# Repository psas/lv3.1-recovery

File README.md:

# LV-3.1 Recovery Repository

The LV-3.1 Electromechanical Recovery System (ERS) is a fully-resettable recovery system for the [PSAS](http://psas.pdx.edu/) Launch Vehicle v 3.1 (LV-3.1). Each ERS "unit" releases a single parachute. The top unit deploys our ballute test parachute that's in the nose cone, the next ERS unit releases a standard drogue, and the final ERS unit releases the main parachute.

## Mechanical CAD
All mechanical CAD has been moved to OnShape and can be found [here](https://cad.onshape.com/documents/03e169a7501c9614bcd8fe34/w/d2206dc55680e29e4d8f6e15/e/43f9d4697ebc459acca1436a).

## Control System

In this Git repo is a PCB with STM32F091 microcontroller that controls the system. See the ControlSystem directory.

## Testing and Analysis

The ERS system will be tested by dropping it from a helicopter over a field. Many parameters must be considered for this test including wind speed, altitude, field size, parachute drag coefficients, and parachute release timing. Analysis of drop test dispersal patterns based on fixing some parameters and simulating variation in others enables us to choose an appropriate drop site and drop parameters. Analysis notebooks can by found in the /analysis directory.

* [Parent Directory](https://github.com/psas/lv3.1-recovery/tree/master/Analysis)
* [Primary mission analysis document](https://github.com/psas/lv3.1-recovery/blob/master/Analysis/Mission_Analysis.ipynb)
* [Jupyter Notebook to run simulations](https://github.com/psas/lv3.1-recovery/blob/master/Analysis/drop_test_simulator.ipynb)

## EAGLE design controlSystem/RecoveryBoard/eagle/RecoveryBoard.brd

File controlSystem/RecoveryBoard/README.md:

# Electromechanical Recovery System (ERS) v4.0 Controller Board 

## General information
This board controls the ERS v4 modules in LV3.1 and hopefully eventually in LV4.

Full documentation can be found [here](https://docs.google.com/document/d/1TOoC-d3vpsw2uvtvazEmFV9_g59nFPVRWKC9Ye5qgKw/edit?usp=sharing)

## Firmware

The firmware is written in C and runs on top of ChibiOS, a small RTOS. See the "firmware" directory. The [oresat-firmware](https://github.com/oresat/oresat-firmware) repository has instructions on how to get started on the tool chain.

## License

All materials in this repo are copyright Portland State Aerospace Society and are licensed under the CERN Open Hardware Licence Version 2 -
Strongly Reciprocal (CERN-OHL-S v2), or any later version. A copy of the license is located in [here](LICENSE.md).

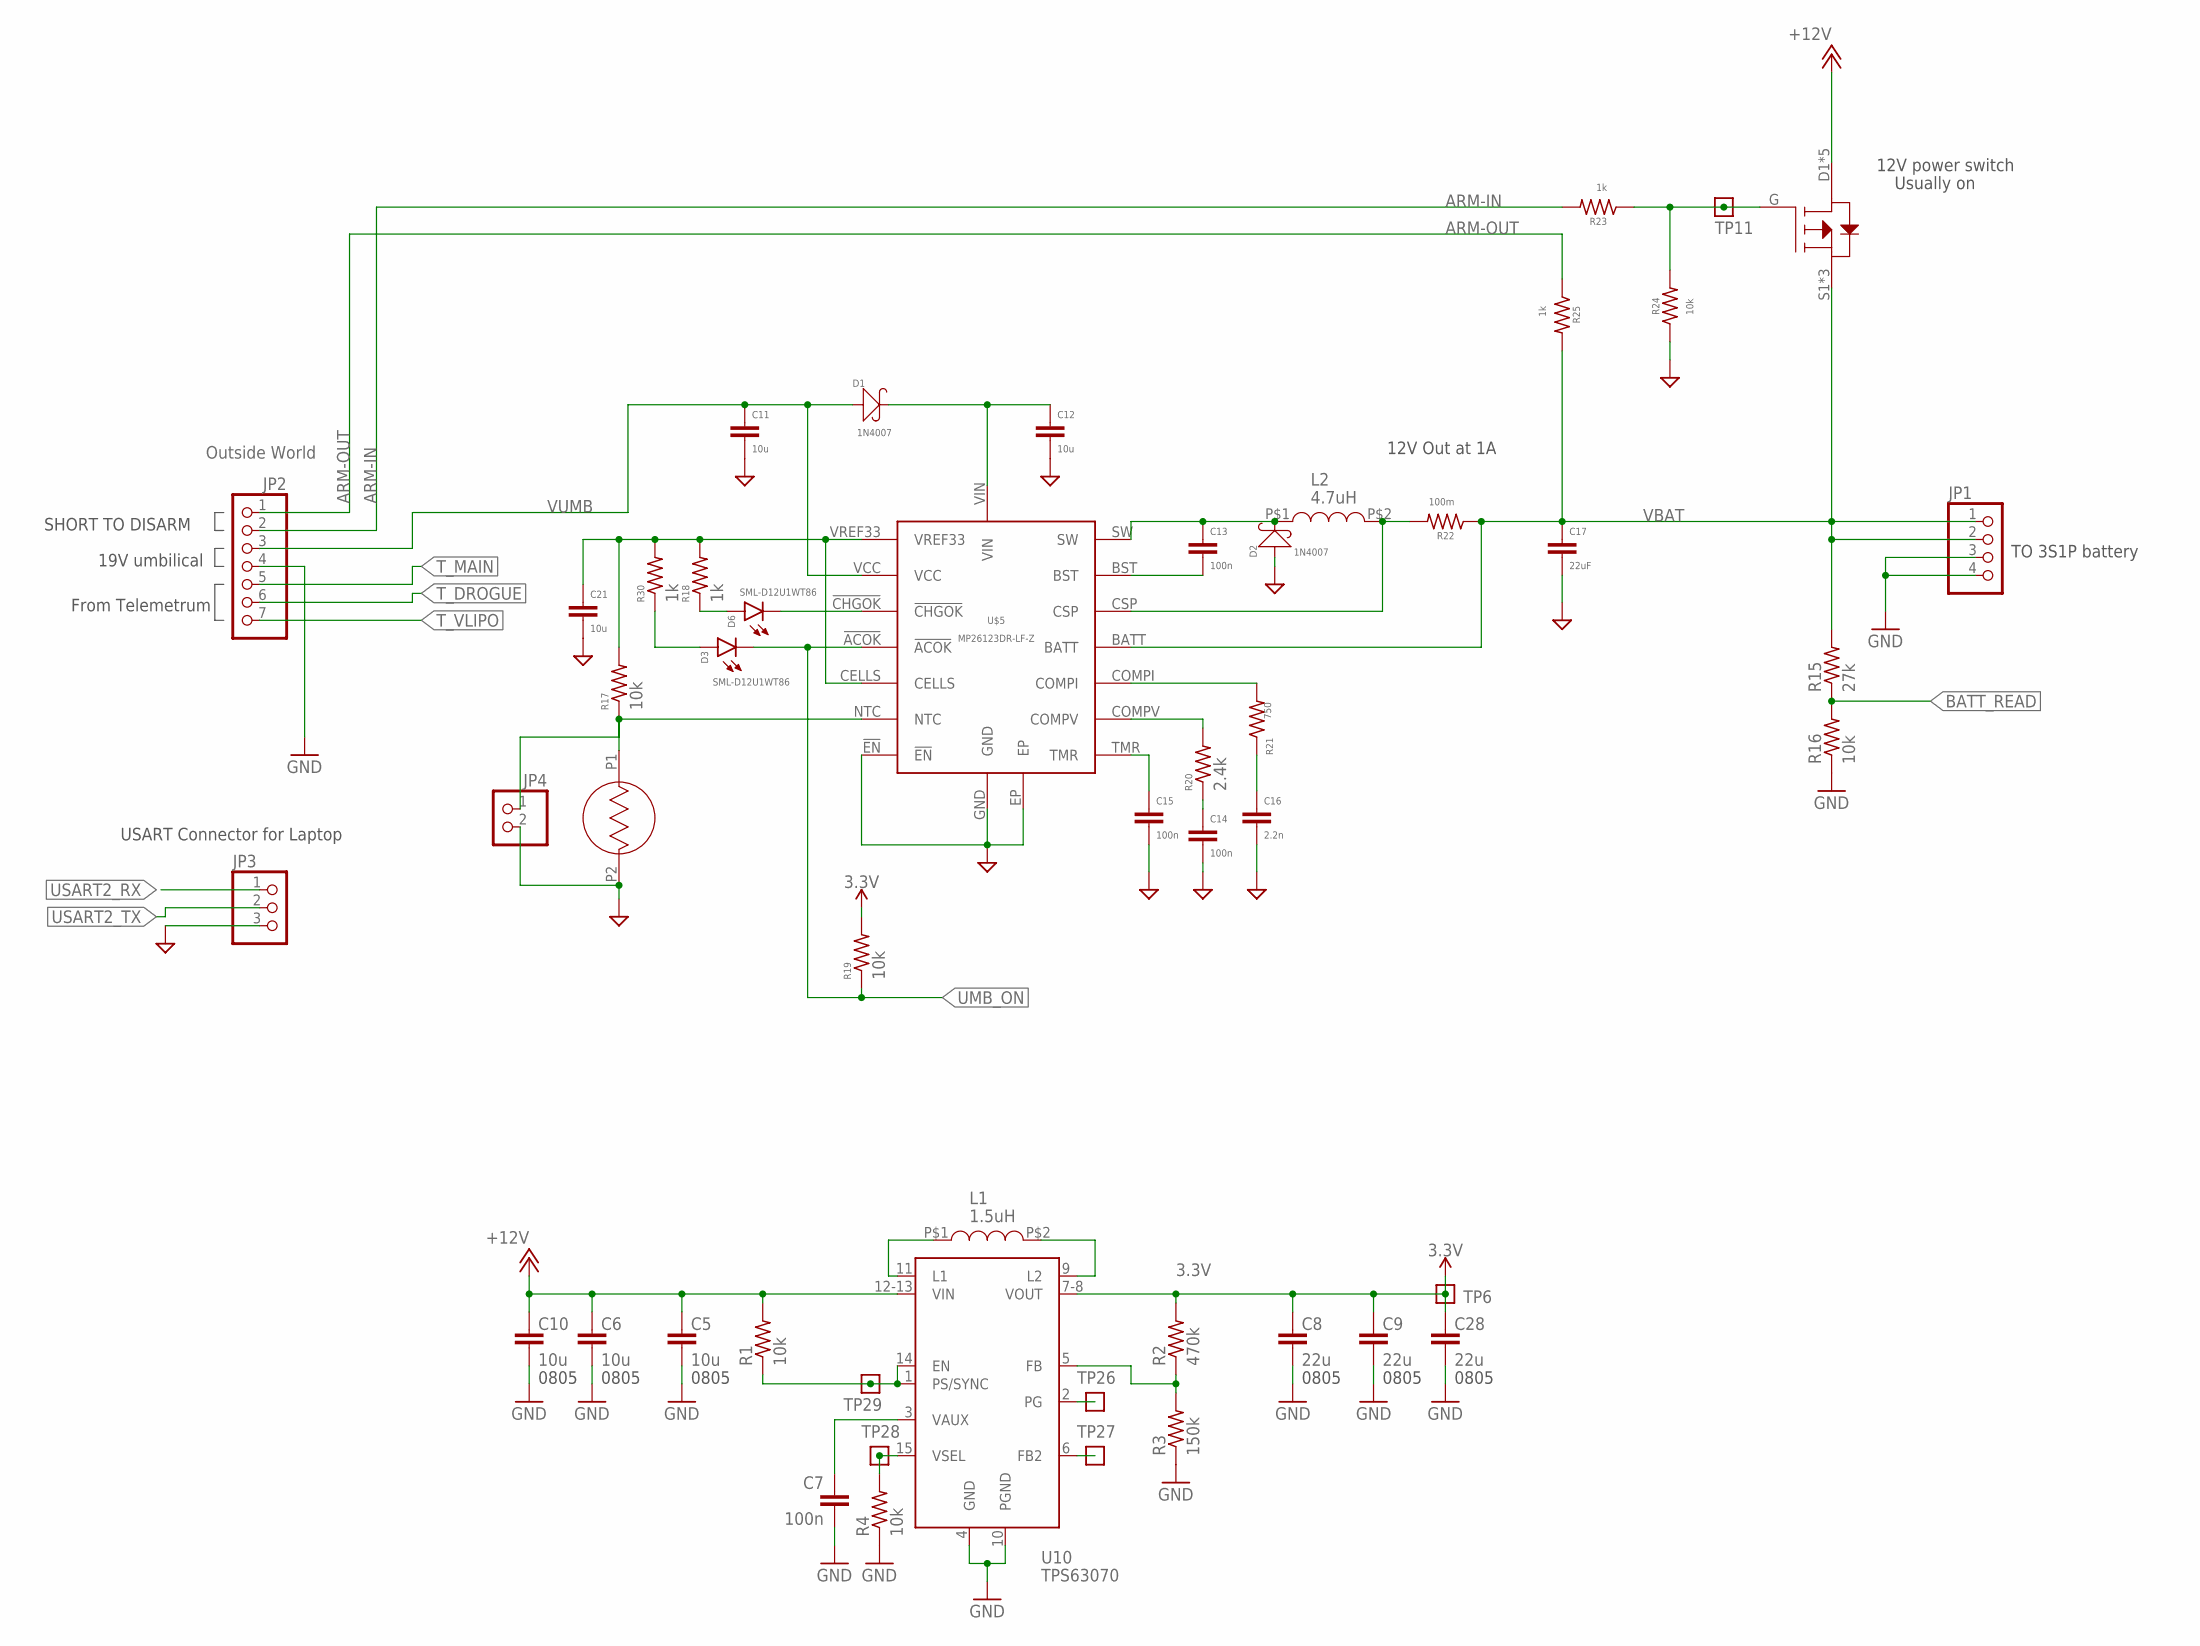
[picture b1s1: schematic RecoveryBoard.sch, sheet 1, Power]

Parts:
C5: 10u; .0805-C-NOSILK; MPN CL05B104KO5NNNC
C6, C10, C11, C12, C21: 10u; .0805-C-NOSILK
C7: 100n; .0603-C-NOSILK; MPN CL05B104KO5NNNC
C8: 22u; .0805-C-NOSILK; MPN CL05B104KO5NNNC
C9, C28: 22u; .0805-C-NOSILK
C13, C14, C15: 100n; .0603-C-NOSILK
C16: 2.2n; .0603-C-NOSILK
C17: 22uF; .0805-C-NOSILK
D1, D2: 1N4007; DO-214AC
D3, D6: SML-D12U1WT86; CHIPLED_0603; MPN SML-D12U1WT86
JP1: PINHD-1X4; 1X04
JP2: PINHD-1X7; 1X07
JP3: PINHD-1X3; 1X03
JP4: PINHD-1X2; 1X02
L1: 1.5uH; IHLP2020CZER1R5M11
L2: 4.7uH; IHLP2020BZER4R7M11
Q7: SI7465DP-T1-E3; SI7465DP-T1-E3CT-ND
R1, R4, R16: 10k; .0603-C-NOSILK; MPN RC1005F6653CS
R2: 470k; .0603-C-NOSILK; MPN RC1005F6653CS
R3: 150k; .0603-C-NOSILK; MPN RC1005F6653CS
R5: NHQ103B375T10
R15: 27k; .0603-C-NOSILK; MPN RC1005F6653CS
R17, R19, R24: 10k; .0603-C-NOSILK
R18, R23, R25, R30: 1k; .0603-C-NOSILK
R20: 2.4k; .0603-C-NOSILK
R21: 750; .0603-C-NOSILK
R22: 100m; 1206-C
TP6, TP11, TP26, TP27, TP28, TP29: TEST-POINT; 2MM-TEST-POINT
U10: TPS63070; TPS63070X
U$5: MP26123DR-LF-Z

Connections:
3.3V: C8.1, C9.1, C28.1, R2.2, R19.2, TP6.1, U10.7-8 (VOUT); also elsewhere on the board
!BEN: C12.1, D1.2 (-), U$5.VIN
+12V: C5.1, C6.1, C10.1, Q7.D1 (D), Q7.D2 (D), Q7.D3 (D), Q7.D4 (D), Q7.DPAD (D), R1.2, U10.12-13 (VIN); also elsewhere on the board
ARM-IN: JP2.2, R23.2
ARM-OUT: JP2.1, R25.1
BATT_READ: R15.1, R16.2; also elsewhere on the board
GND: C5.2, C6.2, C7.2, C8.2, C9.2, C10.2, C11.2, C12.2, C14.2, C15.2, C16.2, C17.2, C21.2, C28.2, D2.1 (+), JP1.3, JP1.4, JP2.4, JP3.3, JP4.2, R3.1, R4.1, R5.P2, R16.1, R24.1, U10.4 (GND), U10.10 (PGND), U$5.!EN, U$5.EP, U$5.GND; also elsewhere on the board
unnamed: C13.1, D2.2 (-), L2.P$1, U$5.SW
unnamed: C13.2, U$5.BST
unnamed: C21.1, R17.2, R18.2, R30.2, U$5.CELLS, U$5.VREF33
unnamed: D6.C, U$5.!CHGOK
unnamed: D3.A, R30.1
unnamed: Q7.G, R23.1, R24.2, TP11.1
unnamed: D6.A, R18.1
unnamed: R20.2, U$5.COMPV
unnamed: C15.1, U$5.TMR
unnamed: JP4.1, R5.P1, R17.1, U$5.NTC
unnamed: R21.2, U$5.COMPI
unnamed: C16.1, R21.1
unnamed: L2.P$2, R22.2, U$5.CSP
unnamed: C14.1, R20.1
TPS-EN: R1.1, TP29.1, U10.1 (PS/SYNC), U10.14 (EN)
TPS-FB: R2.1, R3.2, U10.5 (FB)
TPS-FB2: TP27.1, U10.6 (FB2)
TPS-L1: L1.P$1, U10.11 (L1)
TPS-L2: L1.P$2, U10.9 (L2)
TPS-PG: TP26.1, U10.2 (PG)
TPS-VAUX: C7.1, U10.3 (VAUX)
TPS-VSEL: R4.2, TP28.1, U10.15 (VSEL)
T_DROGUE: JP2.6; also elsewhere on the board
T_MAIN: JP2.5; also elsewhere on the board
T_VLIPO: JP2.7; also elsewhere on the board
UMB_ON: D3.C, R19.1, U$5.!ACOK; also elsewhere on the board
USART2_RX: JP3.1; also elsewhere on the board
USART2_TX: JP3.2; also elsewhere on the board
VBAT: C17.1, JP1.1, JP1.2, Q7.S1 (S), Q7.S2 (S), Q7.S3 (S), R15.2, R22.1, R25.2, U$5.BATT
VUMB: C11.1, D1.1 (+), JP2.3, U$5.VCC

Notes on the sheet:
0805
Outside World
TO 3S1P battery
SHORT TO DISARM
19V umbilical
12V power switch
Usually on
From Telemetrum
USART Connector for Laptop
12V Out at 1A

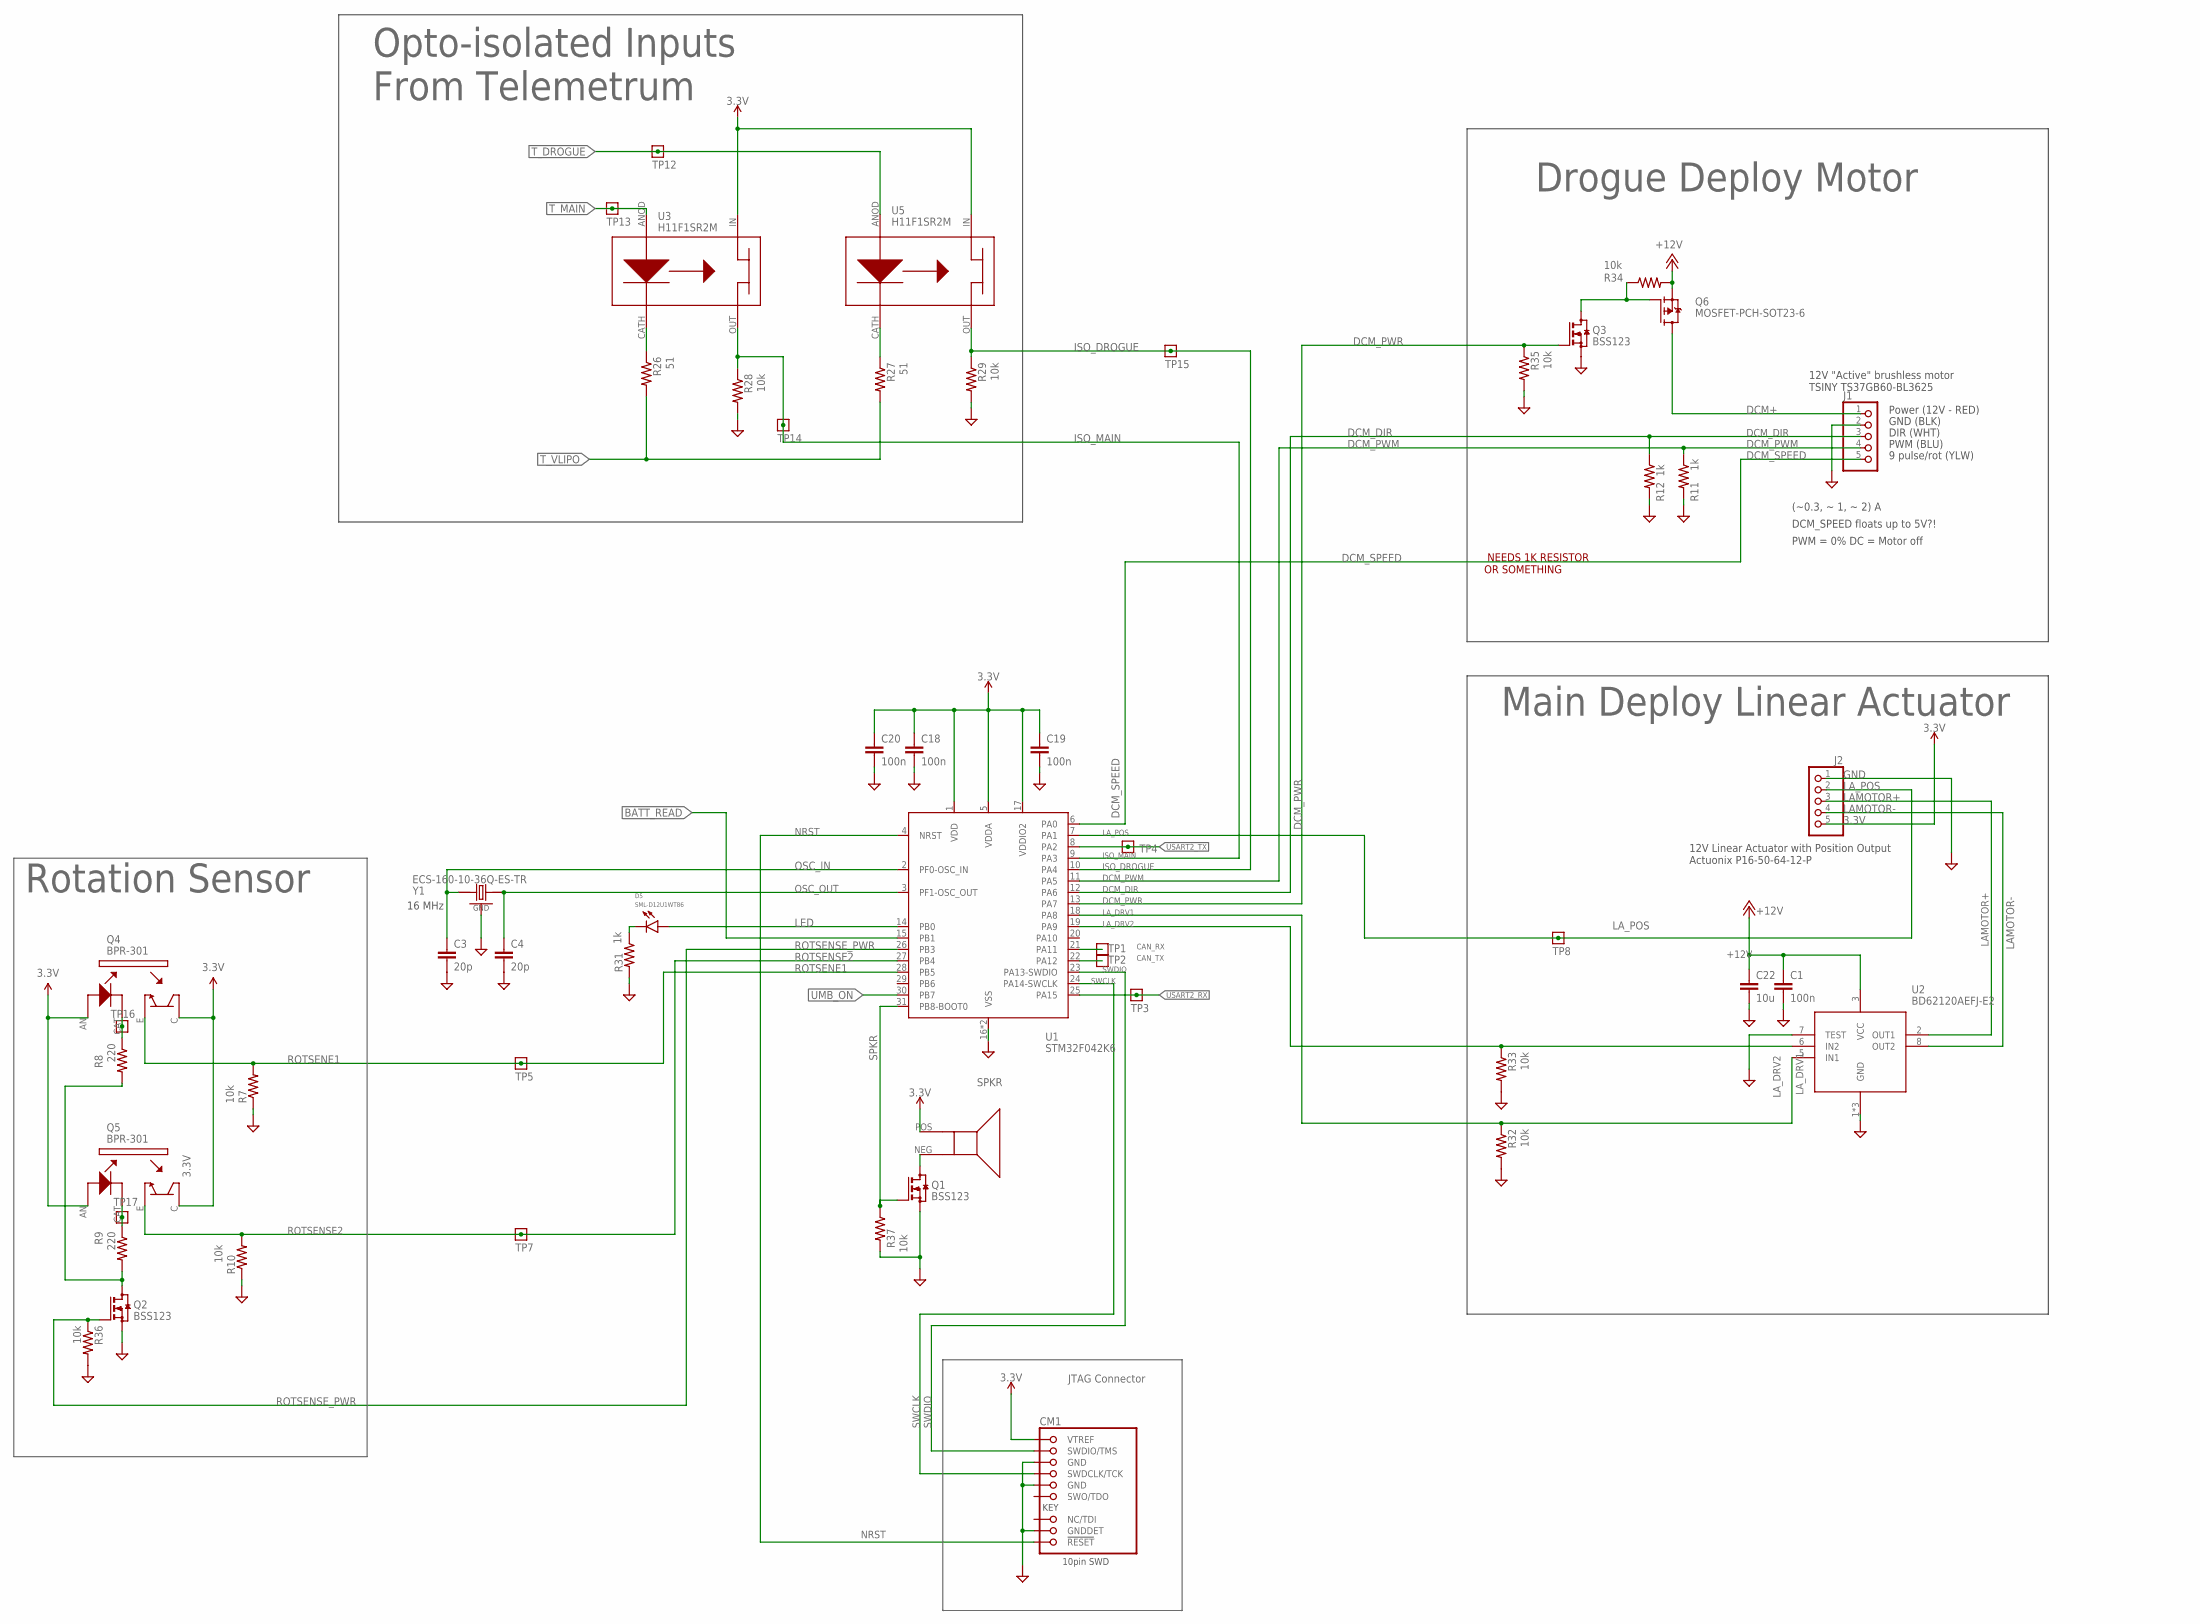
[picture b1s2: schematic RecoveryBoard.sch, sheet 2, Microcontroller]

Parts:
C1, C18, C19, C20: 100n; .0603-C-NOSILK
C3, C4: 20p; .0603-C-NOSILK
C22: 10u; .0805-A-NOSILK
CM1: FTSH-105-XX-X-DV-K; CON10_2X5_DUK_FTSH
D5: SML-D12U1WT86; CHIPLED_0603; MPN SML-D12U1WT86
J1, J2: PINHD-1X5; 1X05
Q1, Q2, Q3: BSS123; SOT23
Q4, Q5: BPR-301
Q6: MOSFET-PCH-SOT23-6; SOT23-6
R7, R10, R28, R29, R32, R33, R34, R35, R36, R37: 10k; .0603-C-NOSILK
R8, R9: 220; .0603-C-NOSILK
R11, R12, R31: 1k; .0603-C-NOSILK
R26, R27: 51; .0603-C-NOSILK
TP1, TP2, TP3, TP4, TP5, TP7, TP8, TP12, TP13, TP14, TP15, TP16, TP17: TEST-POINT; 2MM-TEST-POINT
U1: STM32F042K6; QFP32-7X7
U2: BD62120AEFJ-E2; SOIC127P600X100-9N
U3, U5: H11F1SR2M
U$7: SMT-0440-S-R
Y1: ECS-160-10-36Q-ES-TR; XTAL_ECS-160-10-36Q-ES-TR

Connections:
3.3V: C18.1, C19.1, C20.1, CM1.1 (VTREF), J2.5, Q4.AN (ANOD), Q4.C (COLL), Q5.AN (ANOD), Q5.C (COLL), U1.1 (VDD), U1.5 (VDDA), U1.17 (VDDIO2), U3.IN, U5.IN, U$7.POS; also elsewhere on the board
+12V: C1.1, C22.1, Q6.4 (S), R34.2, U2.3 (VCC); also elsewhere on the board
BATT_READ: U1.15 (PB1); also elsewhere on the board
CAN_RX: TP1.1, U1.21 (PA11)
CAN_TX: TP2.1, U1.22 (PA12)
DCM+: J1.1, Q6.1 (D), Q6.2 (D), Q6.5 (D), Q6.6 (D)
DCM_DIR: J1.3, R12.1, U1.12 (PA6)
DCM_PWM: J1.4, R11.1, U1.11 (PA5)
DCM_PWR: Q3.1 (G), R35.1, U1.13 (PA7)
DCM_SPEED: J1.5, U1.6 (PA0)
GND: C1.2, C3.2, C4.2, C18.2, C19.2, C20.2, C22.2, CM1.3 (GND), CM1.5 (GND), CM1.9 (GNDDET), J1.2, J2.1, Q1.2 (S), Q2.2 (S), Q3.2 (S), R7.1, R10.1, R11.2, R12.2, R28.2, R29.2, R31.2, R32.2, R33.2, R35.2, R36.2, R37.2, U1.16 (VSS), U1.32 (VSS), U2.1 (GND), U2.4 (GND), U2.7 (TEST), U2.9 (GND), Y1.GND, Y1.GND2 (GND); also elsewhere on the board
ISO_DROGUE: R29.1, TP15.1, U1.10 (PA4), U5.OUT
ISO_MAIN: R28.1, TP14.1, U1.9 (PA3), U3.OUT
LAMOTOR+: J2.3, U2.2 (OUT1)
LAMOTOR-: J2.4, U2.8 (OUT2)
LA_DRV1: R32.1, U1.18 (PA8), U2.5 (IN1)
LA_DRV2: R33.1, U1.19 (PA9), U2.6 (IN2)
LA_POS: J2.2, TP8.1, U1.7 (PA1)
LED: D5.A, U1.14 (PB0)
unnamed: Q1.3 (D), U$7.NEG
unnamed: Q4.CAT (CATH), R8.1, TP16.1
unnamed: D5.C, R31.1
unnamed: Q5.CAT (CATH), R9.1, TP17.1
unnamed: Q3.3 (D), Q6.3 (G), R34.1
unnamed: R26.1, U3.CATH (CAT)
unnamed: R27.1, U5.CATH (CAT)
unnamed: Q2.3 (D), R8.2, R9.2
NRST: CM1.10 (!RESET), U1.4 (NRST)
OSC_IN: C3.1, U1.2 (PF0-OSC_IN), Y1.IN/OUT
OSC_OUT: C4.1, U1.3 (PF1-OSC_OUT), Y1.OUT/IN
ROTSENE1: Q4.E (EMIT), R7.2, TP5.1, U1.28 (PB5)
ROTSENSE2: Q5.E (EMIT), R10.2, TP7.1, U1.27 (PB4)
ROTSENSE_PWR: Q2.1 (G), R36.1, U1.26 (PB3)
SPKR: Q1.1 (G), R37.1, U1.31 (PB8-BOOT0)
SWCLK: CM1.4 (SWDCLK/TCK), U1.24 (PA14-SWCLK)
SWDIO: CM1.2 (SWDIO/TMS), U1.23 (PA13-SWDIO)
T_DROGUE: TP12.1, U5.ANOD; also elsewhere on the board
T_MAIN: TP13.1, U3.ANOD; also elsewhere on the board
T_VLIPO: R26.2, R27.2; also elsewhere on the board
UMB_ON: U1.30 (PB7); also elsewhere on the board
USART2_RX: TP3.1, U1.25 (PA15); also elsewhere on the board
USART2_TX: TP4.1, U1.8 (PA2); also elsewhere on the board

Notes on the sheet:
Rotation Sensor
JTAG Connector
12V Linear Actuator with Position Output Actuonix P16-50-64-12-P
12V "Active" brushless motor TSINY TS37GB60-BL3625
Power (12V - RED)
GND (BLK)
DIR (WHT)
PWM (BLU)
9 pulse/rot (YLW)
Opto-isolated Inputs From Telemetrum
Drogue Deploy Motor
Main Deploy Linear Actuator
16 MHz
NEEDS 1K RESISTOR OR SOMETHING
(~0.3, ~ 1, ~ 2) A
DCM_SPEED floats up to 5V?!
PWM = 0% DC = Motor off

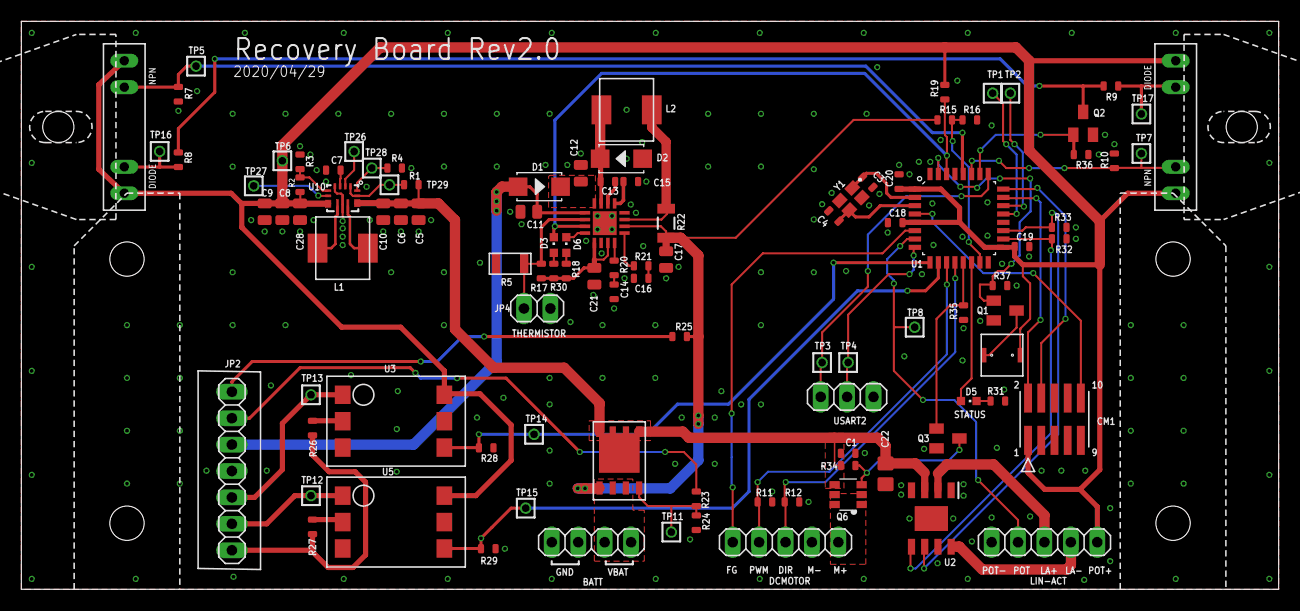
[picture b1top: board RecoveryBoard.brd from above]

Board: 2 copper layers, 120.9 x 54.6 mm, 104 parts (0 on the bottom side), 69 nets.

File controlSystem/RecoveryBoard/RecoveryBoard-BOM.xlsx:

Qty | Parts | MFR | MPN | Description | DIS | DPN
1 | C16 | KEMET | C0603C222K5RAC7411 | 2200pF ±10% 50V Ceramic Capacitor X7R 0603 (1608 Metric) | Digi-Key | 399-17586-1-ND
4 | C8, C9, C28, C17 | Murata Electronics | GRM21BR61E226ME44K | 22µF ±20% 25V Ceramic Capacitor X5R 0805 (2012 Metric) | Digi-Key | 490-14661-1-ND
9 | C1, C7, C13, C14, C15, C18, C19, C20, C22 | Yageo | CC0603KRX5R9BB104 | 0.1µF ±10% 50V Ceramic Capacitor X5R 0603 (1608 Metric) | Digi-Key | 311-4046-1-ND
2 | C3, C4 | KEMET | C0805C200J5GACTU | 20pF ±5% 50V Ceramic Capacitor C0G, NP0 0805 (2012 Metric) | Digi-Key | 399-8033-2-ND
6 | C5, C6, C10, C11, C12, C21 | Murata Electronics | GRM21BR6YA106KE43L | 10µF ±10% 35V Ceramic Capacitor X5R 0805 (2012 Metric) | Digi-Key | 490-10514-1-ND
1 | CM1 | Samtec Inc. | FTSH-105-01-L-DV-K-P-TR | JTAG Connector 10 position 0.050" (1.27mm) | Digi-Key | SAM13164CT-ND
2 | D1, D2 | Diodes Incorporated | S1M-13-F | Diode Standard 1000V 1A Surface Mount SMA | Digi-Key | S1M-FDITR-ND
3 | D3, D5, D6 | Rohm SemiConductor | SML-D12U1WT86 | Red 620nm LED Indication - Discrete 2.2V 0603 (1608 Metric) | Digi-Key | SML-D12U1WT86CT-ND
2 | J1, J2 | TBD | TBD | PINHD-1X5 1X05 PIN HEADER | TBD | TBD
1 | JP1 | TBD | TBD | PINHD-1X4 1X04 PIN HEADER | TBD | TBD
1 | JP2 | TBD | TBD | PINHD-1X7 1X07 PIN HEADER | TBD | TBD
1 | JP3 | TBD | TBD | PINHD-1X3 1X03 PIN HEADER | TBD | TBD
1 | L1 | Vishay Dale | IHLP2020CZER1R5M11 | 1.5µH Shielded Molded Inductor 7.5A 18.5mOhm Max Nonstandard | Digi-Key | 541-1235-1-ND
1 | L2 | Vishay Dale | IHLP2020BZER4R7M11 | 4.7µH Shielded Molded Inductor 3.2A 81.3mOhm Max Nonstandard | Digi-Key | 541-1222-1-ND
3 | Q1, Q2, Q3 | ON Semiconductor | BSS123 | N-Channel 100V 170mA (Ta) 360mW (Ta) Surface Mount SOT-23-3 | Digi-Key | BSS123NCT-ND
2 | Q4, Q5 | American Bright Opto | BPR-301 | Reflective Optical Sensor White Paper Module | Digi-Key | BPR-301-ND
1 | Q6 | STMicroelectronics | STT4P3LLH6 | P-Channel 30V 4A (Ta) 1.6W (Ta) Surface Mount SOT-23-6 | Digi-Key | 497-15521-2-ND
1 | Q7 | Vishay | SI7465DP-T1-E3 | P-Channel 60 V 3.2A (Ta) 1.5W (Ta) Surface Mount PowerPAK® SO-8 | Digi-Key | SI7465DP-T1-E3CT-ND
7 | R11, R12, R18, R23, R25, R30, R31 | Yageo | AC0603FR-071KL | 1 kOhms ±1% 0.1W, 1/10W Chip Resistor 0603 (1608 Metric) | Digi-Key | 311-1KLDCT-ND
1 | R13 | Yageo | AC0603FR-071K8L | 1.8 kOhms ±1% 0.1W, 1/10W Chip Resistor 0603 (1608 Metric) | Digi-Key | 311-1.8KLDCT-ND
1 | R14 | Yageo | AC0603FR-073K3L | 3.3 kOhms ±1% 0.1W, 1/10W Chip Resistor 0603 (1608 Metric) | Digi-Key | YAG3605CT-ND
1 | R15 | Yageo | AC0603FR-0727KL | 27 kOhms ±1% 0.1W, 1/10W Chip Resistor 0603 (1608 Metric) | Digi-Key | YAG3585CT-ND
16 | R1, R4, R7, R10, R16, R17, R19, R24, R28, R29, R32, R33, R34, R35, R36, R37 | Yageo | AC0603FR-0710KL | 10 kOhms ±1% 0.1W, 1/10W Chip Resistor 0603 (1608 Metric) | Digi-Key | 311-10KLDCT-ND
1 | R2 | Yageo | AC0603FR-07470KL | 470 kOhms ±1% 0.1W, 1/10W Chip Resistor 0603 (1608 Metric) | Digi-Key | YAG3609CT-ND
1 | R20 | Yageo | AC0603FR-072K4L | 2.4 kOhms ±1% 0.1W, 1/10W Chip Resistor 0603 (1608 Metric) | Digi-Key | YAG5724CT-ND
1 | R21 | Yageo | AC0603FR-07750RL | 750 Ohms ±1% 0.1W, 1/10W Chip Resistor 0603 (1608 Metric) | Digi-Key | YAG3628CT-ND
1 | R22 | StackPole Electronics Inc | CSR1206FTR100 | 100 mOhms ±1% 0.5W, 1/2W Chip Resistor 1206 Current Sense | Digi-Key | CSR1206FTR100CT-ND
2 | R26, R27 | Yageo | AC0603FR-0751RL | 51 Ohms ±1% 0.1W, 1/10W Chip Resistor 0603 (1608 Metric) | Digi-Key | YAG3617CT-ND
1 | R3 | Yageo | AC0603FR-07150KL | 150 kOhms ±1% 0.1W, 1/10W Chip Resistor 0603 (1608 Metric) | Digi-Key | YAG3567CT-ND
1 | R5 | Yageo | AC0603FR-07100KL | 100 kOhms ±1% 0.1W, 1/10W Chip Resistor 0603 (1608 Metric) | Digi-Key | 311-100KLDCT-ND
2 | R8, R9 | Yageo | AC0603FR-07470RL | 470 Ohms ±1% 0.1W, 1/10W Chip Resistor 0603 (1608 Metric) | Digi-Key | 311-470LDCT-ND
1 | U1 | STMicroelectronics | STM32F042K6T6 | STM32F0 uC IC 32-Bit 48Mhz 32KB (32K x 8) FLASH 32-LQFP (7x7) | Digi-Key | 497-14647-ND
1 | U2 | Rohm SemiConductor | BD62120AEFJ-E2 | Motor Driver DMOS On/Off 8-HTSOP-J | Digi-Key | BD62120AEFJ-E2CT-ND
2 | U3, U4 | ON Semiconductor | H11F1SR2M | Optoisolator MOSFET Output 7500Vpk 1 Channel 6-SMD | Digi-Key | H11F1SR2MCT-ND
1 | U5 | MPS Inc | MP26123DR-LF-Z | Charger IC Lithium-Ion 16-QFN (4x4) | Digi-Key | 1589-1609-1-ND
1 | U6 | Amphenol | NHQ103B375T10 | NTC Thermistor 10k 1206 (3216 Metric) | Digi-Key | 235-1109-1-ND
1 | U7 | PUI Audio Inc. | SMT-0440-S-R | Buzzers 3V 90mA 4kHz 70dB @ 3V, 10cm SMD | Digi-Key | 668-1488-1-ND
1 | U8 | Vishay Siliconix | SI7465DP-T1-E3 | P-Channel 60V 3.2A (Ta) 1.5W (Ta) Surface Mount PowerPAK® SO-8 | Digi-Key | SI7465DP-T1-E3CT-ND
1 | U10 | Texas Instruments | TPS630702RNMT | Buck-Boost SPS Positive Adjustable 2.5V 2A | Digi-Key | 296-TPS630702RNMTCT-ND
1 | Y1 | ECS Inc. | ECS-160-10-36Q-ES-TR | 16MHz ±30ppm Crystal 10pF 80 Ohms 4-SMD, No Lead | Digi-Key | XC2181CT-ND

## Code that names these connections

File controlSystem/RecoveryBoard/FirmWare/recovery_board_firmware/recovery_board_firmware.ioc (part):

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Mcu.Name=STM32F042K(4-6)Tx
Mcu.Package=LQFP32
Mcu.UserName=STM32F042K6Tx
PA1.GPIOParameters=GPIO_Label
PA1.GPIO_Label=LA_POS
PA1.Mode=IN1
PA1.Signal=ADC_IN1
PA11.Mode=Master
PA11.Signal=CAN_RX
PA12.Mode=Master
PA12.Signal=CAN_TX
PA13.Mode=Serial_Wire
PA13.Signal=SYS_SWDIO
PA14.Mode=Serial_Wire
PA14.Signal=SYS_SWCLK
PA15.GPIOParameters=GPIO_ModeDefaultPP,GPIO_Speed,GPIO_PuPd
PA15.GPIO_ModeDefaultPP=GPIO_MODE_AF_PP
PA15.GPIO_PuPd=GPIO_NOPULL
PA15.GPIO_Speed=GPIO_SPEED_FREQ_HIGH
PA15.Mode=Asynchronous
PA15.Signal=USART2_RX
PA2.GPIOParameters=GPIO_ModeDefaultPP,GPIO_Speed,GPIO_PuPd
PA2.GPIO_ModeDefaultPP=GPIO_MODE_AF_PP
PA2.GPIO_PuPd=GPIO_NOPULL
PA2.GPIO_Speed=GPIO_SPEED_FREQ_HIGH
PA2.Mode=Asynchronous
PA2.Signal=USART2_TX
PA3.GPIOParameters=GPIO_PuPd,GPIO_Label,GPIO_Mode
PA3.GPIO_Label=ISO_CHUTE
PA3.GPIO_Mode=GPIO_MODE_INPUT
PA3.GPIO_PuPd=GPIO_NOPULL
PA3.Signal=GPIO_Input
PA4.GPIOParameters=GPIO_PuPd,GPIO_Label,GPIO_Mode
PA4.GPIO_Label=ISO_DROGUE
PA4.GPIO_Mode=GPIO_MODE_INPUT
PA4.GPIO_PuPd=GPIO_NOPULL
PA4.Signal=GPIO_Input
PA5.GPIOParameters=GPIO_Speed,PinState,GPIO_PuPd,GPIO_Label,GPIO_ModeDefaultOutputPP
PA5.GPIO_Label=DCM_DIR
PA5.GPIO_ModeDefaultOutputPP=GPIO_MODE_OUTPUT_PP
PA5.GPIO_PuPd=GPIO_NOPULL
PA5.GPIO_Speed=GPIO_SPEED_FREQ_LOW
PA5.PinState=GPIO_PIN_RESET
PA5.Signal=GPIO_Output
PA6.GPIOParameters=GPIO_Label
PA6.GPIO_Label=DCM_PWM
PA6.Signal=S_TIM3_CH1
PA7.GPIOParameters=GPIO_Speed,PinState,GPIO_PuPd,GPIO_Label,GPIO_ModeDefaultOutputPP
PA7.GPIO_Label=DCM_ON
PA7.GPIO_ModeDefaultOutputPP=GPIO_MODE_OUTPUT_PP
PA7.GPIO_PuPd=GPIO_NOPULL
PA7.GPIO_Speed=GPIO_SPEED_FREQ_LOW
PA7.PinState=GPIO_PIN_RESET
PA7.Signal=GPIO_Output
PA8.GPIOParameters=GPIO_Speed,PinState,GPIO_PuPd,GPIO_Label,GPIO_ModeDefaultOutputPP
PA8.GPIO_Label=LA_IN1
PA8.GPIO_ModeDefaultOutputPP=GPIO_MODE_OUTPUT_PP
PA8.GPIO_PuPd=GPIO_NOPULL
PA8.GPIO_Speed=GPIO_SPEED_FREQ_LOW
PA8.PinState=GPIO_PIN_RESET
PA8.Signal=GPIO_Output
PA9.GPIOParameters=GPIO_Speed,GPIO_FMA9,PinState,GPIO_PuPd,GPIO_Label,GPIO_ModeDefaultOutputPP
PA9.GPIO_FMA9=__NULL
PA9.GPIO_Label=LA_IN2
PA9.GPIO_ModeDefaultOutputPP=GPIO_MODE_OUTPUT_PP
PA9.GPIO_PuPd=GPIO_NOPULL
PA9.GPIO_Speed=GPIO_SPEED_FREQ_LOW
PA9.PinState=GPIO_PIN_RESET
PA9.Signal=GPIO_Output
PB0.GPIOParameters=GPIO_Speed,PinState,GPIO_PuPd,GPIO_Label,GPIO_ModeDefaultOutputPP
PB0.GPIO_Label=LED
PB0.GPIO_ModeDefaultOutputPP=GPIO_MODE_OUTPUT_PP
PB0.GPIO_PuPd=GPIO_NOPULL
PB0.GPIO_Speed=GPIO_SPEED_FREQ_LOW
PB0.PinState=GPIO_PIN_RESET
PB0.Signal=GPIO_Output
PB1.GPIOParameters=GPIO_Label
PB1.GPIO_Label=BATT_READ
PB1.Mode=IN9
PB1.Signal=ADC_IN9
PB3.GPIOParameters=GPIO_Speed,PinState,GPIO_PuPd,GPIO_Label,GPIO_ModeDefaultOutputPP
PB3.GPIO_Label=SENSOR_ON
PB3.GPIO_ModeDefaultOutputPP=GPIO_MODE_OUTPUT_PP
PB3.GPIO_PuPd=GPIO_NOPULL
PB3.GPIO_Speed=GPIO_SPEED_FREQ_LOW
PB3.PinState=GPIO_PIN_RESET
PB3.Signal=GPIO_Output
PB4.GPIOParameters=GPIO_Label
PB4.GPIO_Label=SENSOR2
PB4.Signal=GPIO_Input
PB5.GPIOParameters=GPIO_PuPd,GPIO_Label,GPIO_Mode
PB5.GPIO_Label=SENSOR1
PB5.GPIO_Mode=GPIO_MODE_INPUT
PB5.GPIO_PuPd=GPIO_NOPULL
PB5.Signal=GPIO_Input
PB7.GPIOParameters=GPIO_Speed,PinState,GPIO_PuPd,GPIO_Label,GPIO_ModeDefaultOutputPP,GPIO_FM7
PB7.GPIO_FM7=__NULL
PB7.GPIO_Label=ACOK
PB7.GPIO_ModeDefaultOutputPP=GPIO_MODE_OUTPUT_PP
PB7.GPIO_PuPd=GPIO_NOPULL
PB7.GPIO_Speed=GPIO_SPEED_FREQ_LOW
PB7.PinState=GPIO_PIN_RESET
PB7.Signal=GPIO_Output
PB8.GPIOParameters=GPIO_Label
PB8.GPIO_Label=SPKR
PB8.Signal=S_TIM16_CH1
PF0-OSC_IN.Mode=HSE-External-Clock-Source
PF0-OSC_IN.Signal=RCC_OSC_IN
RCC.SYSCLKFreq_VALUE=8000000
board=NUCLEO-F042K6
boardIOC=true

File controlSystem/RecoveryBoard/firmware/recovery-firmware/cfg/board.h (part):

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/*
 * GPIOA setup:
 *
 * PA0  - Hall Sensor 1          	(Input, Analog).
 * PA1  - Hall Sensor 2    		    (Input, Analog).
 * PA2  - USART2_TX          		(Digital, Serial).
 * PA3  - AUSART2_RX       		    (Digital, Serial).
 * PA4  - Motor Current Limit       (Output, Analog).
 * PA5  - ISO Drogue         		(Input, Digital).
 * PA6  - ISO Main                  (Input, Digital).
 * PA7  - Rocket Ready              (Output, Digital).
 * PA8  - Umbilical On              (Input, Digital).
 * PA9  - CAN Silent                (CAN line).
 * PA10 - CAN SHDN                  (CAN line).
 * PA11 - CAN RX                    (CAN line).
 * PA12 - CAN TX                    (CAN line).
 * PA13 - SWDIO                     (alternate 0).
 * PA14 - SWCLK                     (alternate 0).
 * PA15 - PIN15                     (input pullup).
 */
#define VAL_GPIOA_MODER             (PIN_MODE_INPUT(GPIOA_HALL_1) |         \
                                     PIN_MODE_INPUT(GPIOA_HALL_2) |         \
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/*
 * GPIOB setup:
 *
 * PB0  - Battery Read          	(Input, Analog).
 * PB1  - Motor Current Sensor      (Input, Analog).
 * PB2  - PIN2                      (bah).
 * PB3  - SWO ARD_D3                (alternate 0).
 * PB4  - Deploy 1                  (Output, Digital, PWM).
 * PB5  - Deploy 2                  (Output, Digital, PWM).
 * PB6  - Motor Power Saver         (Output, Digital, Active Low).
 * PB7  - Motor Failure Sense 	    (Output, Digital, Active Low).
 * PB8  - ARD_D15                   (input pullup).
 * PB9  - ARD_D14                   (input pullup).
 * PB10 - Board Address LSB         (Input, Digital).
 * PB11 - Board Address MSB         (Input, Digital).
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/*
 * GPIOF setup:
 *
 * PF0  - OSC_IN                    (input floating).
 * PF1  - OSC_OUT                   (input floating).
 * PF2  - PIN2                      (input pullup).
 * PF3  - PIN3                      (input pullup).
 * PF4  - PIN4                      (input pullup).
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
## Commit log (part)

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2025-10-31 Fix bug in can_reader
    The conditional compilation scope should be around this entire arm of
    the match statement, otherwise the main board will send out the drogue
    acknowledgement message
2025-10-31 Rename TELEMETRUM_HEARTBEAT_ID -> SENDER_HEARTBEAT_ID
    It's not the telemetrum that sends the heartbeat its the sender board
2025-11-01 Write README for src/bin
2025-11-01 Rename *_STATUS_ID -> *_HEARTBEAT_ID
    Clarity
2025-11-01 Move motor consts to motor module
2025-11-01 Write src README.md
    README explains the shared modules found in src dir
    Fix typo
2025-11-01 Update py can testing scripts
2025-11-01 rename test_can.py -> echo_can.py
    pytest looks for files named test_*.py, so this would conflict with it's
    usage. Also, this is just a clearer name for the purpose of the script
2025-11-02 Write pytests to verify acknowledgement of deployment CAN messages
    These two tests should send messages to the drogue and main boards and
    verify they respond with appropriate acknowledgement messages.
2025-11-02 update gitignore to ignore pycache
2025-11-02 Update src/bin/README.md
    parachute motor constants moved to src/motor.rs
2025-11-02 Update src/README.md
    echo_can task to be used with echo_can.py, not test_can.py
2025-11-02 Fix buffer overflow when recording motor_isense csv
    If the motor runs for longer than expected the buffer holding the csv
    values can overflow. I added a check that makes sure that wont happen
2025-11-07 Add flash memory storage of motor actuations
    Create a flash driver and mutex and use it to store the number of times
    the motor has been actuated. Create cli commands to print and erase this
    data.
2025-11-13 use BOARD env var instead of feature flags to manage parachute boards
    Instead of using feature flags, which aren't supposed to be mutually
    exclusive, use the BOARD environment variable to flash the parachute
    image to either the main or the drogue board. For the main board, set
    BOARD = "main", or for the drogue board set BOARD = "drogue"
2025-11-13 Make reading the ring position non_blocking
    Using try_get instead of changed when reading the ring position will
    allow the heartbeat and "pos" cli command to tell users that the ring is
    not yet intialized instead of blocking until it is initialized.
2025-11-13 Add embedded-test crate and config
    Embedded test is probe-rs's testing suite for running tests on board.
    This commit adds the crate with some necessary configs in the Cargo.toml
    as well as creates a tests directory, blinky sample test, and adds the
    necessary linker args to the build.rs file.
2025-11-20 Make flashing drogue vs main board easier
    Instead of hard coding the environment variable in .cargo/config.toml,
    you can now specify the BOARD environment variable through a commmand
    line override. This was previously not possible because setting it
    through the command line wouldnt trigger a rerun of the build. Adjusting
    the build.rs file fixed this issue. I also wrote cargo aliases to
    simplify the flash commands, and updated the READMEs.
2025-12-28 fix typo
    Config.toml should've been Cargo.toml
2025-12-28 Update README
    Clarify that there is no separate build command to call when
    building/flashing, but add build command if needed.
2026-01-27 variable renames for clarity, update shorepow state in sender
2026-02-04 add parachute boards status ok as dependency to rocket ready
2026-02-04 state of ers boards was using incorrect bit
    0 is the ring position, 5 is the ready state
2026-02-04 make status messages for ers status clearer
    ERR doesn't really make sense. ok or not ready is clearer.
2026-02-04 Fix ers ready state
    position 2 is inbetween, 3 is locked
2026-02-04 display the sensor state when pos uart command is executed
    the uart pos command will now show both the raw adc values as well as
    the calculated ring state of those values for debugging purposes
2026-02-11 Fix RocketReady logic
2026-02-17 Update state commands on all boards
    Now there is an Id field for each board that will print its name, which
    is different from how the chute boards were before. They would only
    print a number and the sender didn't have a id field at all. Keep in
    mind the sender doesnt have an actual field in its state for this
    because its static. I also print a delta from the last seen values
    rather than a time stamp so you dont have to do the math in your head
2026-03-03 Store sensor limits in flash and add cli cmd to change or print them
2026-03-03 Update Readmes
2026-03-23 enable independent watchdog on all 3 boards
    iwdg to recover from hard crashes
2026-03-23 change wdg timing to be more reasonable
2026-03-24 Use buffered CAN driver
    There are some arcane transient errors happening once every 15 to 20
    avionics system tests where the sender will not send a CAN message in
    response to the telemetrum signal to deploy. Buffered CAN should be more
    resilient in theory and so might help with this issue.
2026-03-30 upgrade crates and refactor
2026-03-31 Bugfix: Drogue not releasing reliably in resp to CAN msg
    drogue was releasing slowly or sometimes not at all when CAN messages
    were sent to it. I discovered the motor mutex was not being released
    because there was no inner scope, so I added one. I also moved the
    acknowledge CAN messages for both parachute boards to after the
    deployment happens because drogue was acknowledging even when it didnt
    release. These changes seem to fix the bug.
2026-04-01 bugfix: sender not sending CAN messages reliably
    the parachute boards were sending multiple acknowledgment messages. the
    sender would reset the acknowledgment atomic to false, but then
    immediately set it back to true. We also use a signal instead of a watch
    for the motor i_sense hoping to avoid it immediately returning
    read_until_pos due to stale values in the watch.
2026-04-02 Better error handling
    rather than call .unwrap() on things, I have gone through and tried to
    propagate errors and handle them instead. When unwrap or expect is the
    simplest option, I've replaced them with defmt's unwrap instead of the
    builtin as it should use less resources.
2026-04-02 bugfix: sender heartbeat CAN spam
    I was checking the wrong time for whether or not to send the heartbeat
    message. Changed to time_now and it fixed the error
2026-04-02 bugfix: fix inverted shore power on logic
    high means shorepower is off, low means it's on
2026-04-02 bugfix: unlocking ring when shore power is on
    this is maybe not a "bug" but it is a safety concern. we should never be
    unlocking th rings when shorepower is on. this prevents that.
2026-04-02 move motor ring pos receiver into ::new function
    we don't need to recreate the ring pos receiver every time we run the
    motor. this is a minor optimization but anything to keep the motor
    running operation as lean as possible is a good thing in my opinion.
2026-04-02 run broadcast_ring_position task more often
    this may or may not be necessary but since running the motor will wait
    for this task, doing it more often seems smart
2026-04-02 clean up info logs
2026-04-25 bugfix/rocket ready logic error
    Fix two errors where rocket ready was assumed to be active high, but
    it's actually active low. This was being masked by another error where
    rocket ready was being asserted when shorepower was on.
2026-05-04 Overhaul docs
    The docs were not good before. Also they became heavily out of date over
    time. I've reduced their verbosity as much as I could, and moved as much
    of the explanations of things to comments and the tops of modules.
2026-05-04 create DISABLE_BEEP environment variable
    The beeps will now be on by default but can be turned off by flashing
    with DISABLE_BEEP=true
2026-05-04 More docs clean up
2026-05-04 fix bug with disable_beep cfg
    forgot to make buzz_mode mut, linter didnt care because it doesnt use
    cfgs so it never thought it was being changed. also suppress some lints
    that occur because of cfg directives. Tested and working as normal on
    sender board
2026-05-06 bugfix, CAN deploy message
    We should ignore the 100us continuity check the stratologger does when
    powering off. Also, panicing when there's an error sending the can
    deploy message is not a good idea, for now just log the error and keep
    going.
2026-05-06 remove all calls to panic!()
2026-05-08 Fix bugs preventing flashing
    Mostly just syntax errors, but I will need to figure out how to not
    panic inside the error handler when making the strings for the limits
    command
2026-05-08 Fix freezing when CAN bus is down bug
    When the CAN bus is down, if the telemetrum fires it will hold on to the
    shore power pin mutex until it can send a can message. The main thread
    will wait until it can unlock this mutex before it does anything else so
    that it can update state. this means if the CAN bus can't send the
    deploy message, nothing else can happen.
2026-05-13 Log ignoring sub 10ms firing signal

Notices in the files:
controlSystem/RecoveryBoard/firmware/recovery-firmware/cfg/board.h:
ChibiOS - Copyright (C) 2006..2020 Giovanni Di Sirio
Licensed under the Apache License, Version 2.0 (the "License");
parts and their libraries:
SparkFun-PowerSymbols: Licensing: Creative Commons ShareAlike 4.0 International - https://creativecommons.org/licenses/by-sa/4.0
